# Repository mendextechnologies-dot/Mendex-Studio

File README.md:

# Mendex Engineering Studio v0.1.0 — foundation

**Codex v1.5 workstream:** this review branch extends the released foundation with an 18-entry Tool Center, generic synthetic job queue, logs/evidence previews, reports and dataset-provenance UI. Frozen Agent 1/Agent 2 interface: `12b56c3` / `contracts/v1.5.0`. See [implementation status](docs/IMPLEMENTATION_STATUS.md), [integration usage](docs/INTEGRATIONS.md) and [Agent 2 handoff](docs/AGENT2_HANDOFF.md). Native connector code is not merged or automatically trusted, and this branch is not a full-v1.5 release.

Local Python/PySide6 desktop with SQLite products, typed specifications, immutable previous revisions, filesystem workspaces, native-tool discovery, manual evidence records and draft reports. No engineering calculations or simulation results are produced by the application.

## Install and run (PowerShell)

Tested Python runtime: 3.13.7 x64. Runtime diagnostics report Windows 11 build 26300; the initial Windows marketing-name query returned Windows 10 Home. Only this development workstation has been tested; other machines remain unqualified.

Repository: https://github.com/mendextechnologies-dot/Mendex-Studio · working branch: `main`.

Clone and bootstrap (Git, Python 3.13 and VS Code must be separately installed):

```powershell
git clone https://github.com/mendextechnologies-dot/Mendex-Studio.git
cd Mendex-Studio
powershell -NoProfile -ExecutionPolicy Bypass -File scripts/bootstrap.ps1
.venv\Scripts\python -m mendex_ui
```

The bootstrap sets up only this repository's virtual environment, runs local tests and Doctor, and never installs native engineering tools. `ExecutionPolicy Bypass` applies only to that PowerShell invocation; it does not change system policy.

Equivalent manual setup:

```powershell
python -m venv .venv
.venv\Scripts\python -m pip install -r requirements-lock.txt
.venv\Scripts\python -m pip install -e . --no-deps
.venv\Scripts\python -m pytest -q
.venv\Scripts\python -m mendex_ui
```

Use `--root C:\YourDataFolder` to select a different data directory. Both UI and CLI default to the current directory. Never delete `.mendex` to upgrade; back up `.mendex` and `products` together with the application closed.

```powershell
.venv\Scripts\python -m mendex_core.cli create MC-100 "Transformer pilot" --owner "Engineer"
.venv\Scripts\python -m mendex_core.cli products
.venv\Scripts\python -m mendex_core.cli tools
```

Create products in Products, edit the typed JSON specification, save, then create R002 to preserve R001. Null fields mean unspecified; SI field names carry units. Revision snapshots copy specifications only; native CAD files are not automatically copied. Archived specifications cannot be edited.

## Engineering workflow

1. Select a product and revision in Products. Engineering module screens show its native-file folders and required inputs.
2. Open Tool Manager. Use discovery or browse to an installed executable and Save path. FOUND_UNVERIFIED means compatibility and benchmarks are pending, not ready to simulate. Unknown versions remain unknown. No native tool is launched.
3. Open Validation and record a manual check. The default NOT_EVALUATED entry needs a check ID, reviewer and notes. To record PASS/FAIL, attach an actual evidence file (up to 50 MiB), supply a value and SI unit, and enter minimum and/or maximum. The requested status must match that inclusive numerical criterion. All values, evidence classifications and reviewer identities are manually supplied.
4. Open Reports, Generate draft dossier, select it and Open selected report. The HTML and `snapshot.json` contain frozen specifications, validation history, hashes, tool inventory and warnings. No released status is available.
5. In Products, use Open in VS Code to open the selected revision folder, Open workspace for File Explorer, or Open project file for an associated native application. Files must be inside that revision workspace and use a supported document/CAD extension. Scripts and executables cannot be opened through this action. VS Code, Windows associations and CAD applications must already be installed.
6. In Tool Manager, Run workstation doctor or Export diagnostics. Exports stay under `.mendex/diagnostics`; review environment paths before sharing.
7. In Knowledge Center, review category-specific Engineering rules, loaded/rejected Plugins and the AI interface's explicit availability response. No provider or network connection is configured; no AI-generated engineering answer is produced.
8. In Simulations, record an availability request. It persists the input snapshot and tool metadata as NOT_SUPPORTED, with no solver start or result. This is a job-model foundation, not a simulation runner.

Draft revisions can be renamed or placed In Review. Review locks specification edits until returned to Draft; archived baselines cannot be reopened. Neither state grants product approval. Export specification creates a new JSON snapshot under requirements/; the database remains canonical. Product and specification edits save atomically. Evidence files keep their original name in metadata and use compact internal paths; Open selected evidence checks the hash before invoking an allowed document association.

Evidence copies and metadata are append-only through the service. If specifications change, existing check records remain historical and their effective status becomes NOT_EVALUATED. Missing/modified evidence also becomes NOT_EVALUATED on recheck. Creating a new revision starts a new validation history. Reports do not infer an overall approval from historical PASS entries.

```powershell
.venv\Scripts\python -m mendex_core.cli validation --revision <revision-uuid>
.venv\Scripts\python -m mendex_core.cli report --revision <revision-uuid>
.venv\Scripts\python -m mendex_core.cli open-vscode --revision <revision-uuid>
.venv\Scripts\python -m mendex_core.cli open-file --revision <revision-uuid> requirements/spec.json
.venv\Scripts\python -m mendex_core.doctor --export
.venv\Scripts\python -m mendex_core.cli rules
.venv\Scripts\python -m mendex_core.cli plugins
.venv\Scripts\python -m mendex_core.cli request-simulation --revision <revision-uuid> --tool ltspice
.venv\Scripts\python -m mendex_core.cli runs --revision <revision-uuid>
.venv\Scripts\python scripts/desktop_smoke.py
```

Doctor returns exit code 0 when the Python/Qt/SQLite framework is usable. Its workstation status remains PARTIAL while native tools and benchmarks are unqualified. BLOCKED or invalid CLI operations return a nonzero exit code with actionable JSON diagnostics. A successful process handoff does not prove a CAD application opened or executed correctly.

To verify a non-editable wheel installation in a fresh environment on this workstation:

```powershell
powershell -NoProfile -ExecutionPolicy Bypass -File scripts/verify_install.ps1
```

This retains the verification environment in ignored `.mendex/qa`; it does not replace a second-engineer clean-machine acceptance test. See [manual acceptance](docs/manual-acceptance.md) for the remaining release gates.

Database schema v3 migrates existing v1/v2 data automatically and preserves evidence. Before upgrading, close Studio and back up `.mendex` and `products` together. To roll back the application, restore the matching pre-upgrade backup; do not open v3 data with an older build. HTML/JSON are the supported draft formats; Word/PDF export remains a post-foundation enhancement.

Data-only plugins can extend discovery and rules using [the template](templates/plugins/example-discovery.json); see [configuration instructions](config/README.md). The loader rejects invalid/conflicting manifests without importing Python. Built-in metadata and rule resources ship inside the wheel. Tool versions are read from available Windows file metadata; runtime compatibility remains unqualified.

Manual primary-workstation handoff and packaging commands:

```powershell
.venv\Scripts\python scripts/interactive_acceptance.py --launch
powershell -NoProfile -ExecutionPolicy Bypass -File scripts/package.ps1
```

The first command opens actual VS Code, File Explorer and a harmless uniquely named text fixture, observes the matching windows and retains an acceptance record under ignored `.mendex/qa`. The second requires committed sources, runs local tests and produces a wheel/source archive/checksums under `dist`. Neither command runs a simulator, controls hardware or deploys software. The [v0.1 requirements matrix](docs/requirements-matrix.md) records what is implemented and what the final addendum explicitly excludes.

See [implementation checklist](docs/implementation-checklist.md), [architecture](docs/architecture.md) and [known limitations](docs/known-limitations.md). No CI/CD or deployments are configured.

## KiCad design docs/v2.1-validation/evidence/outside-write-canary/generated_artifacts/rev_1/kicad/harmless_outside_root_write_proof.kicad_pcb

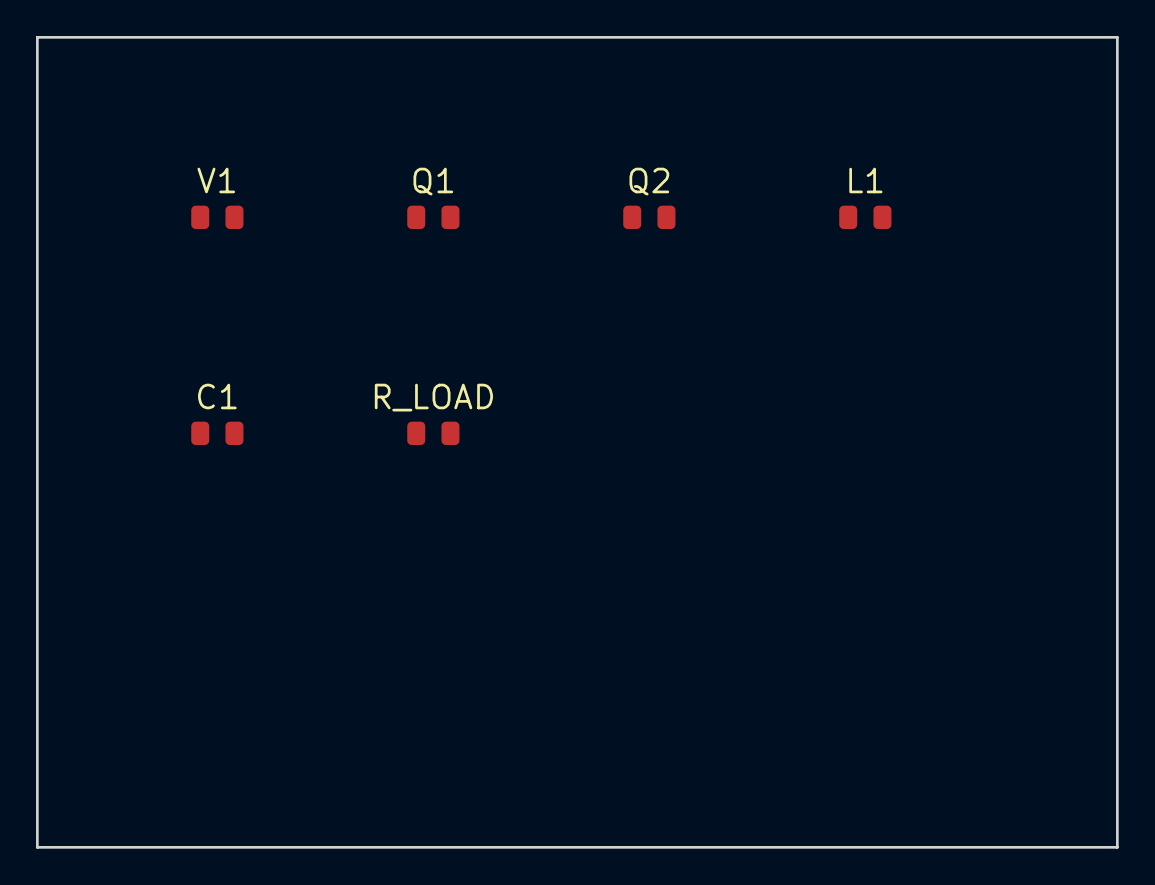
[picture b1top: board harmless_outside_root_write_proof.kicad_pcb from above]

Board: 2 copper layers, 60.0 x 45.0 mm, 6 parts (0 on the bottom side), 2 nets, no tracks yet.

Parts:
C1: Output Filter Capacitor; R_0805_2012Metric
L1: Power Inductor; R_0805_2012Metric
Q1: High-Side Switch; R_0805_2012Metric
Q2: Synchronous Low-Side Switch; R_0805_2012Metric
R_LOAD: Load Resistor; R_0805_2012Metric
V1: Input DC Supply; R_0805_2012Metric

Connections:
SW: C1.2, L1.2, Q1.2, Q2.2, R_LOAD.2, V1.2
VIN: C1.1, L1.1, Q1.1, Q2.1, R_LOAD.1, V1.1

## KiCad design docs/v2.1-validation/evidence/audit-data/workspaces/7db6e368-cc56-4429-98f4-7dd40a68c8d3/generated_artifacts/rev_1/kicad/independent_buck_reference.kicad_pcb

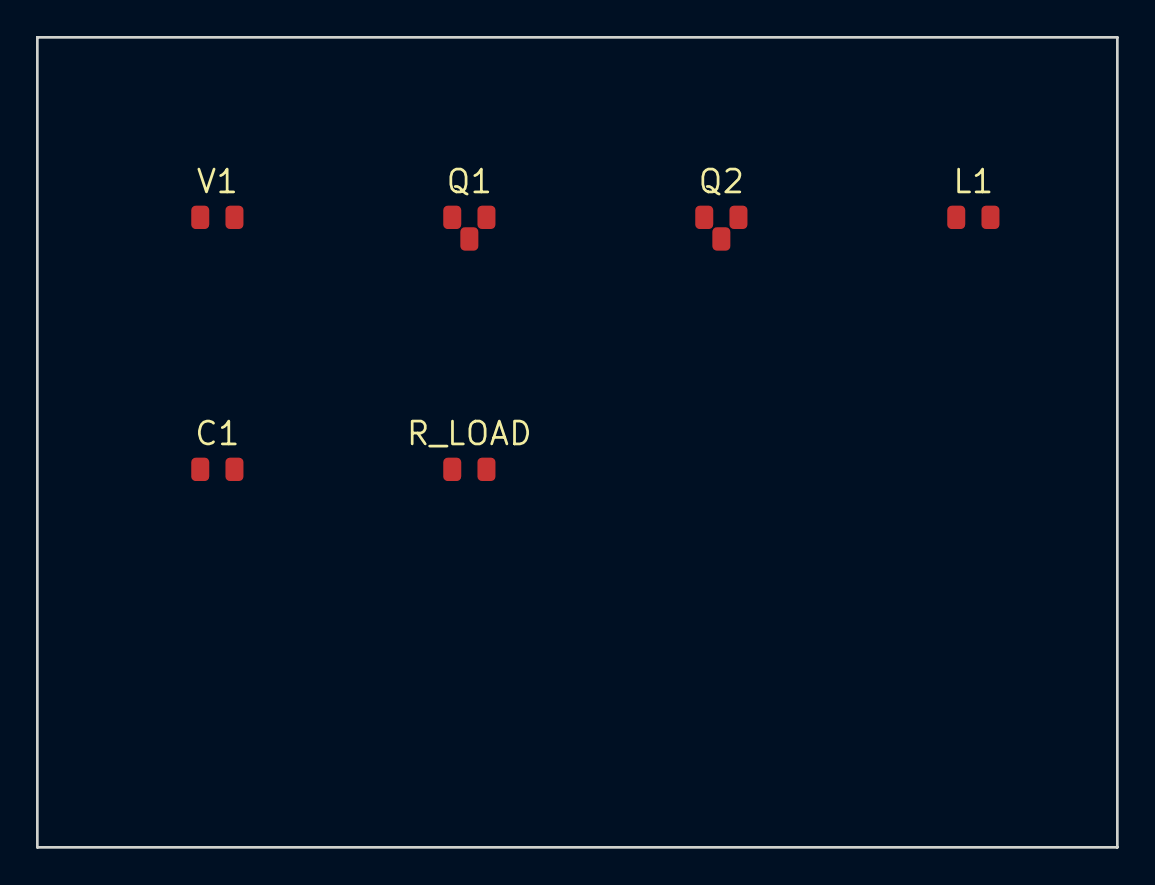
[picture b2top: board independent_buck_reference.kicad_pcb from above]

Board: 2 copper layers, 60.0 x 45.0 mm, 6 parts (0 on the bottom side), 4 nets, no tracks yet.

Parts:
C1: Output Filter Capacitor; R_0805_2012Metric
L1: Power Inductor; R_0805_2012Metric
Q1: High-Side Switch; R_0805_2012Metric
Q2: Synchronous Low-Side Switch; R_0805_2012Metric
R_LOAD: Load Resistor; R_0805_2012Metric
V1: Input DC Supply; R_0805_2012Metric

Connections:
GND: C1.2, Q2.s, R_LOAD.2, V1.n
SW: L1.1, Q1.s, Q2.d
VIN: Q1.d, V1.p
VOUT: C1.1, L1.2, R_LOAD.1

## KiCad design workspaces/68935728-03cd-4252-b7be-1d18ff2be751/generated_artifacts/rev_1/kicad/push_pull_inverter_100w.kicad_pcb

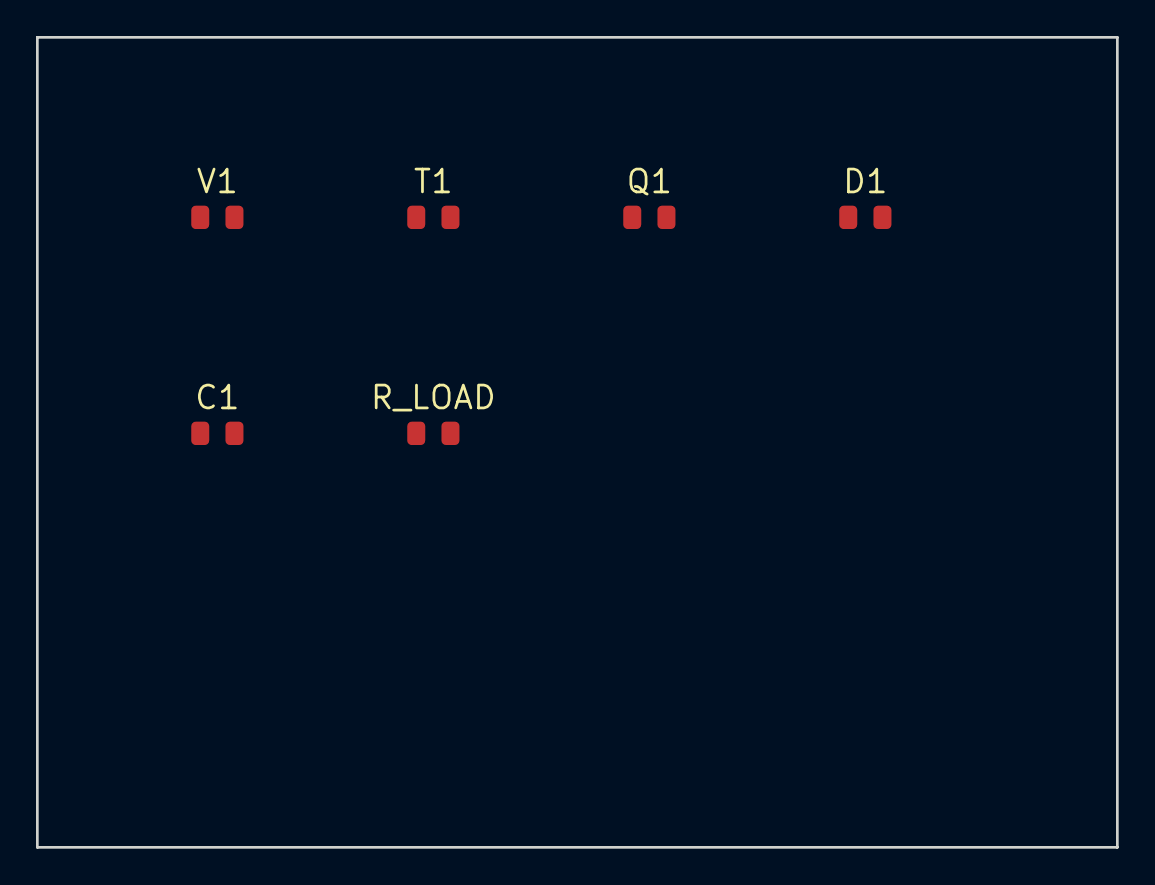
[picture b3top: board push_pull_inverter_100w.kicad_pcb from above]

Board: 2 copper layers, 60.0 x 45.0 mm, 6 parts (0 on the bottom side), 2 nets, no tracks yet.

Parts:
C1: Secondary Output Capacitor; R_0805_2012Metric
D1: Secondary Rectifier Diode; R_0805_2012Metric
Q1: Primary Switching MOSFET; R_0805_2012Metric
R_LOAD: Output Load; R_0805_2012Metric
T1: Coupled Flyback Transformer; R_0805_2012Metric
V1: Input DC Supply; R_0805_2012Metric

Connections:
DRAIN: C1.2, D1.2, Q1.2, R_LOAD.2, T1.2, V1.2
VIN: C1.1, D1.1, Q1.1, R_LOAD.1, T1.1, V1.1
